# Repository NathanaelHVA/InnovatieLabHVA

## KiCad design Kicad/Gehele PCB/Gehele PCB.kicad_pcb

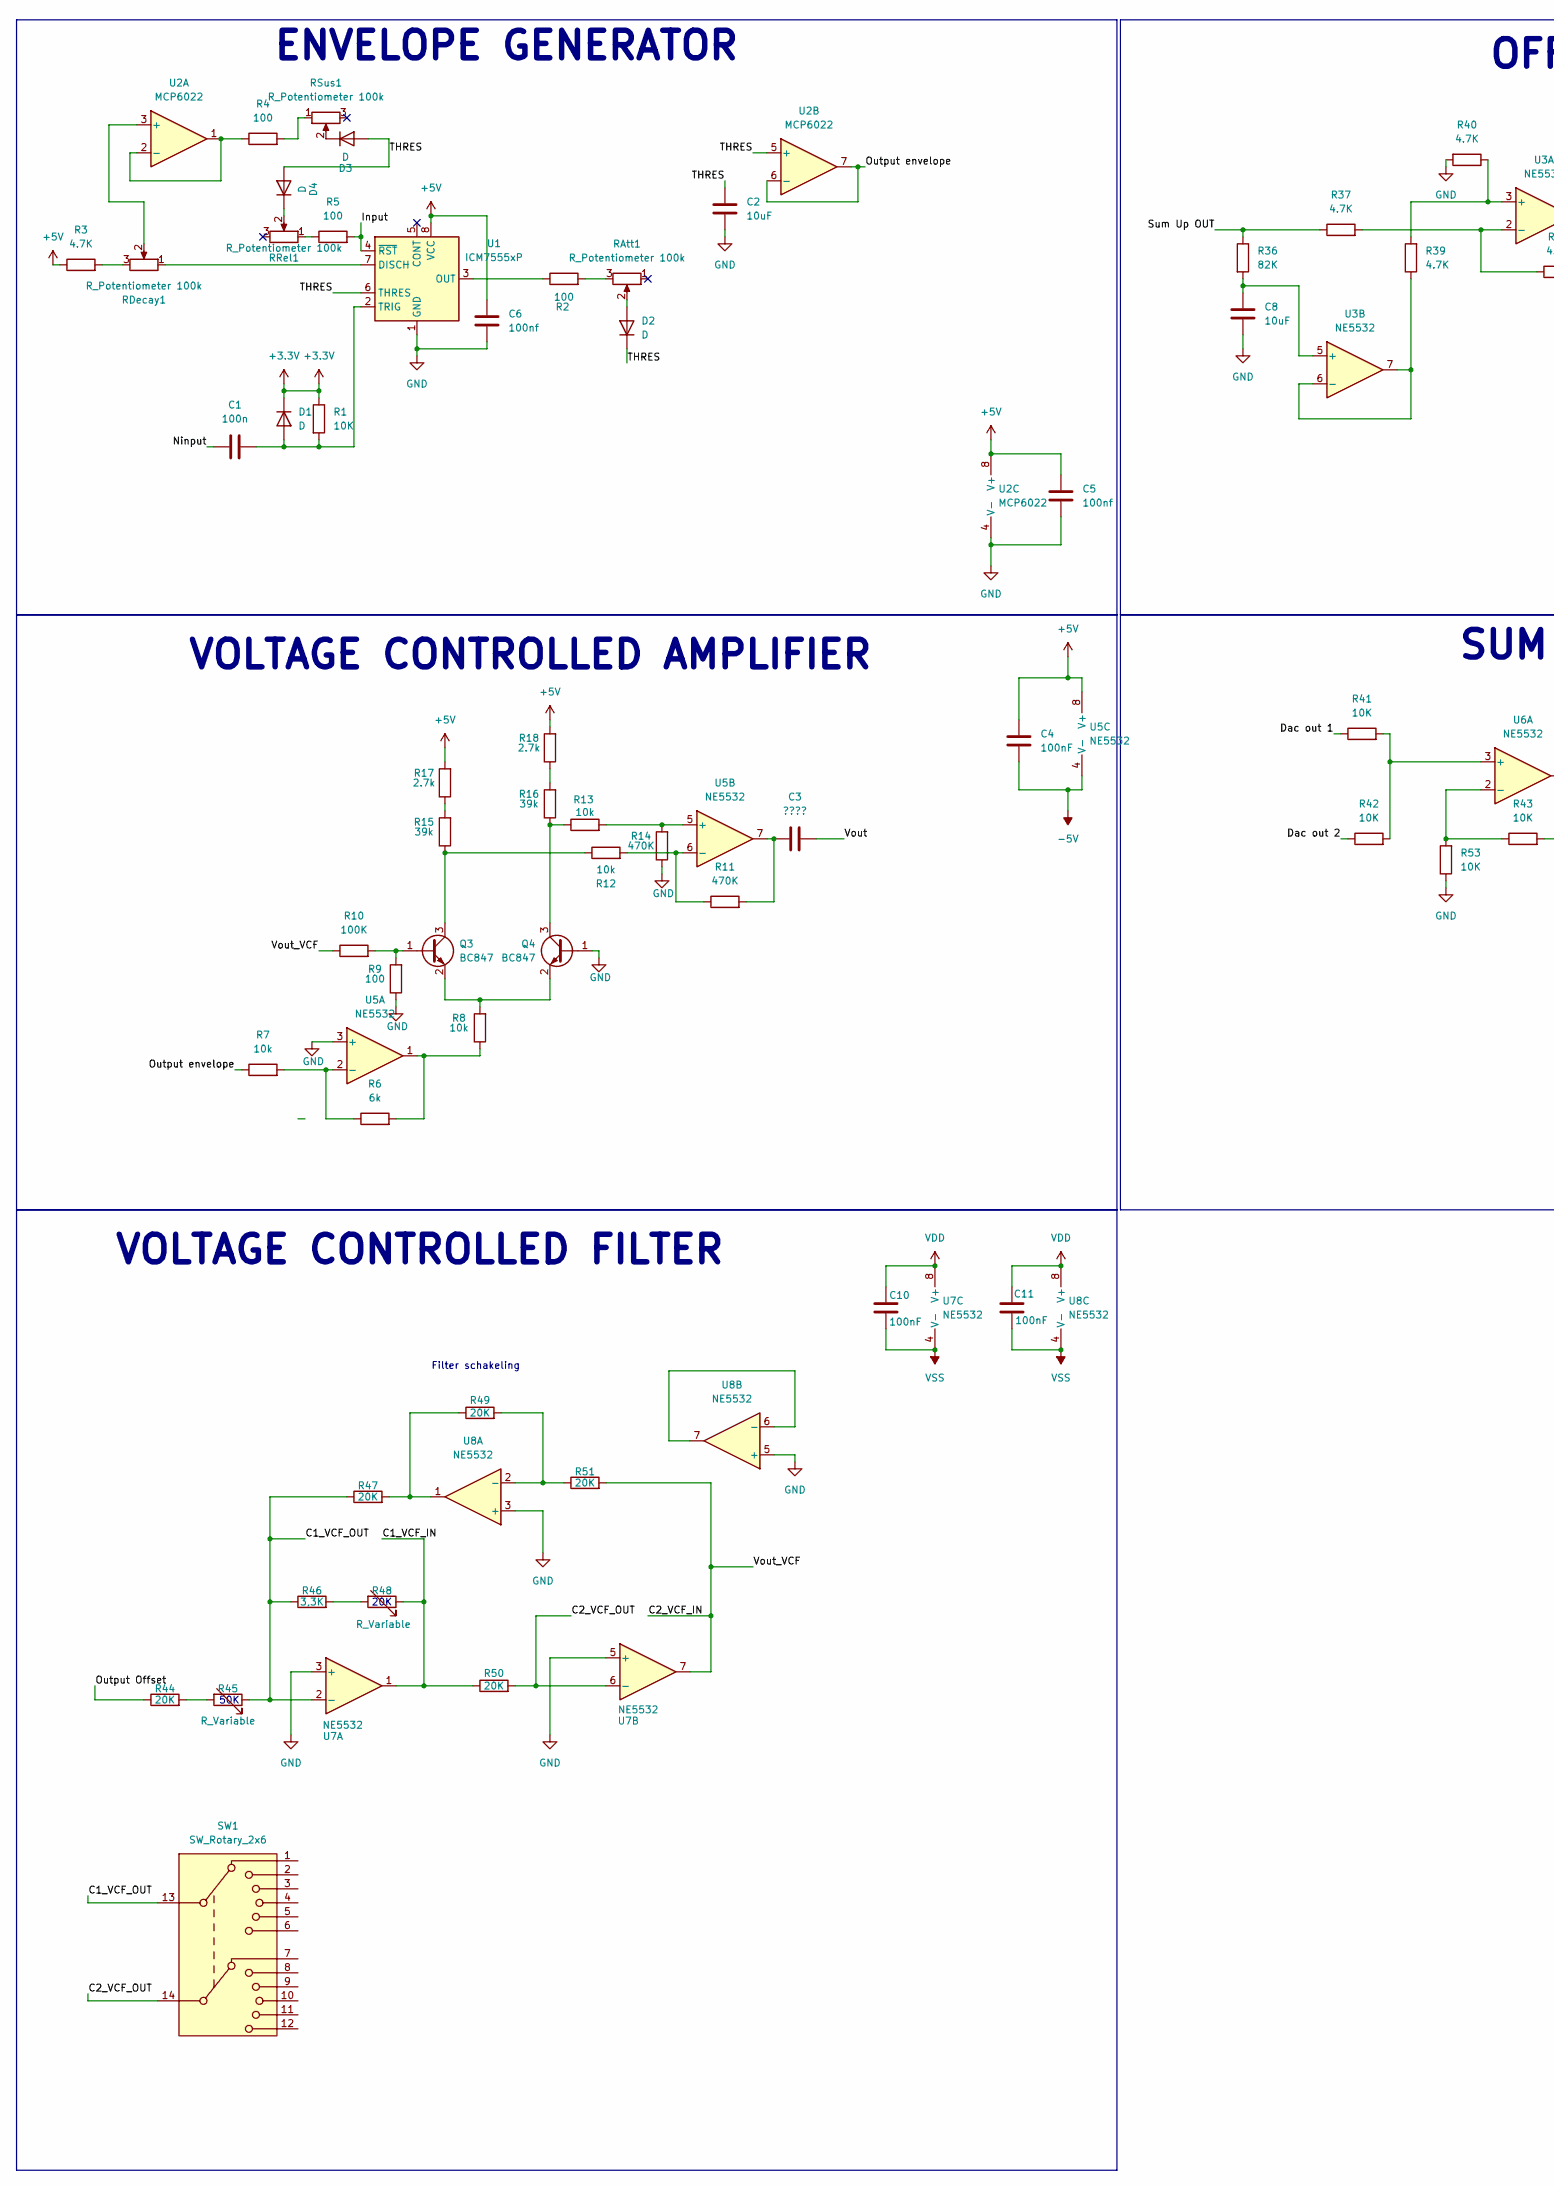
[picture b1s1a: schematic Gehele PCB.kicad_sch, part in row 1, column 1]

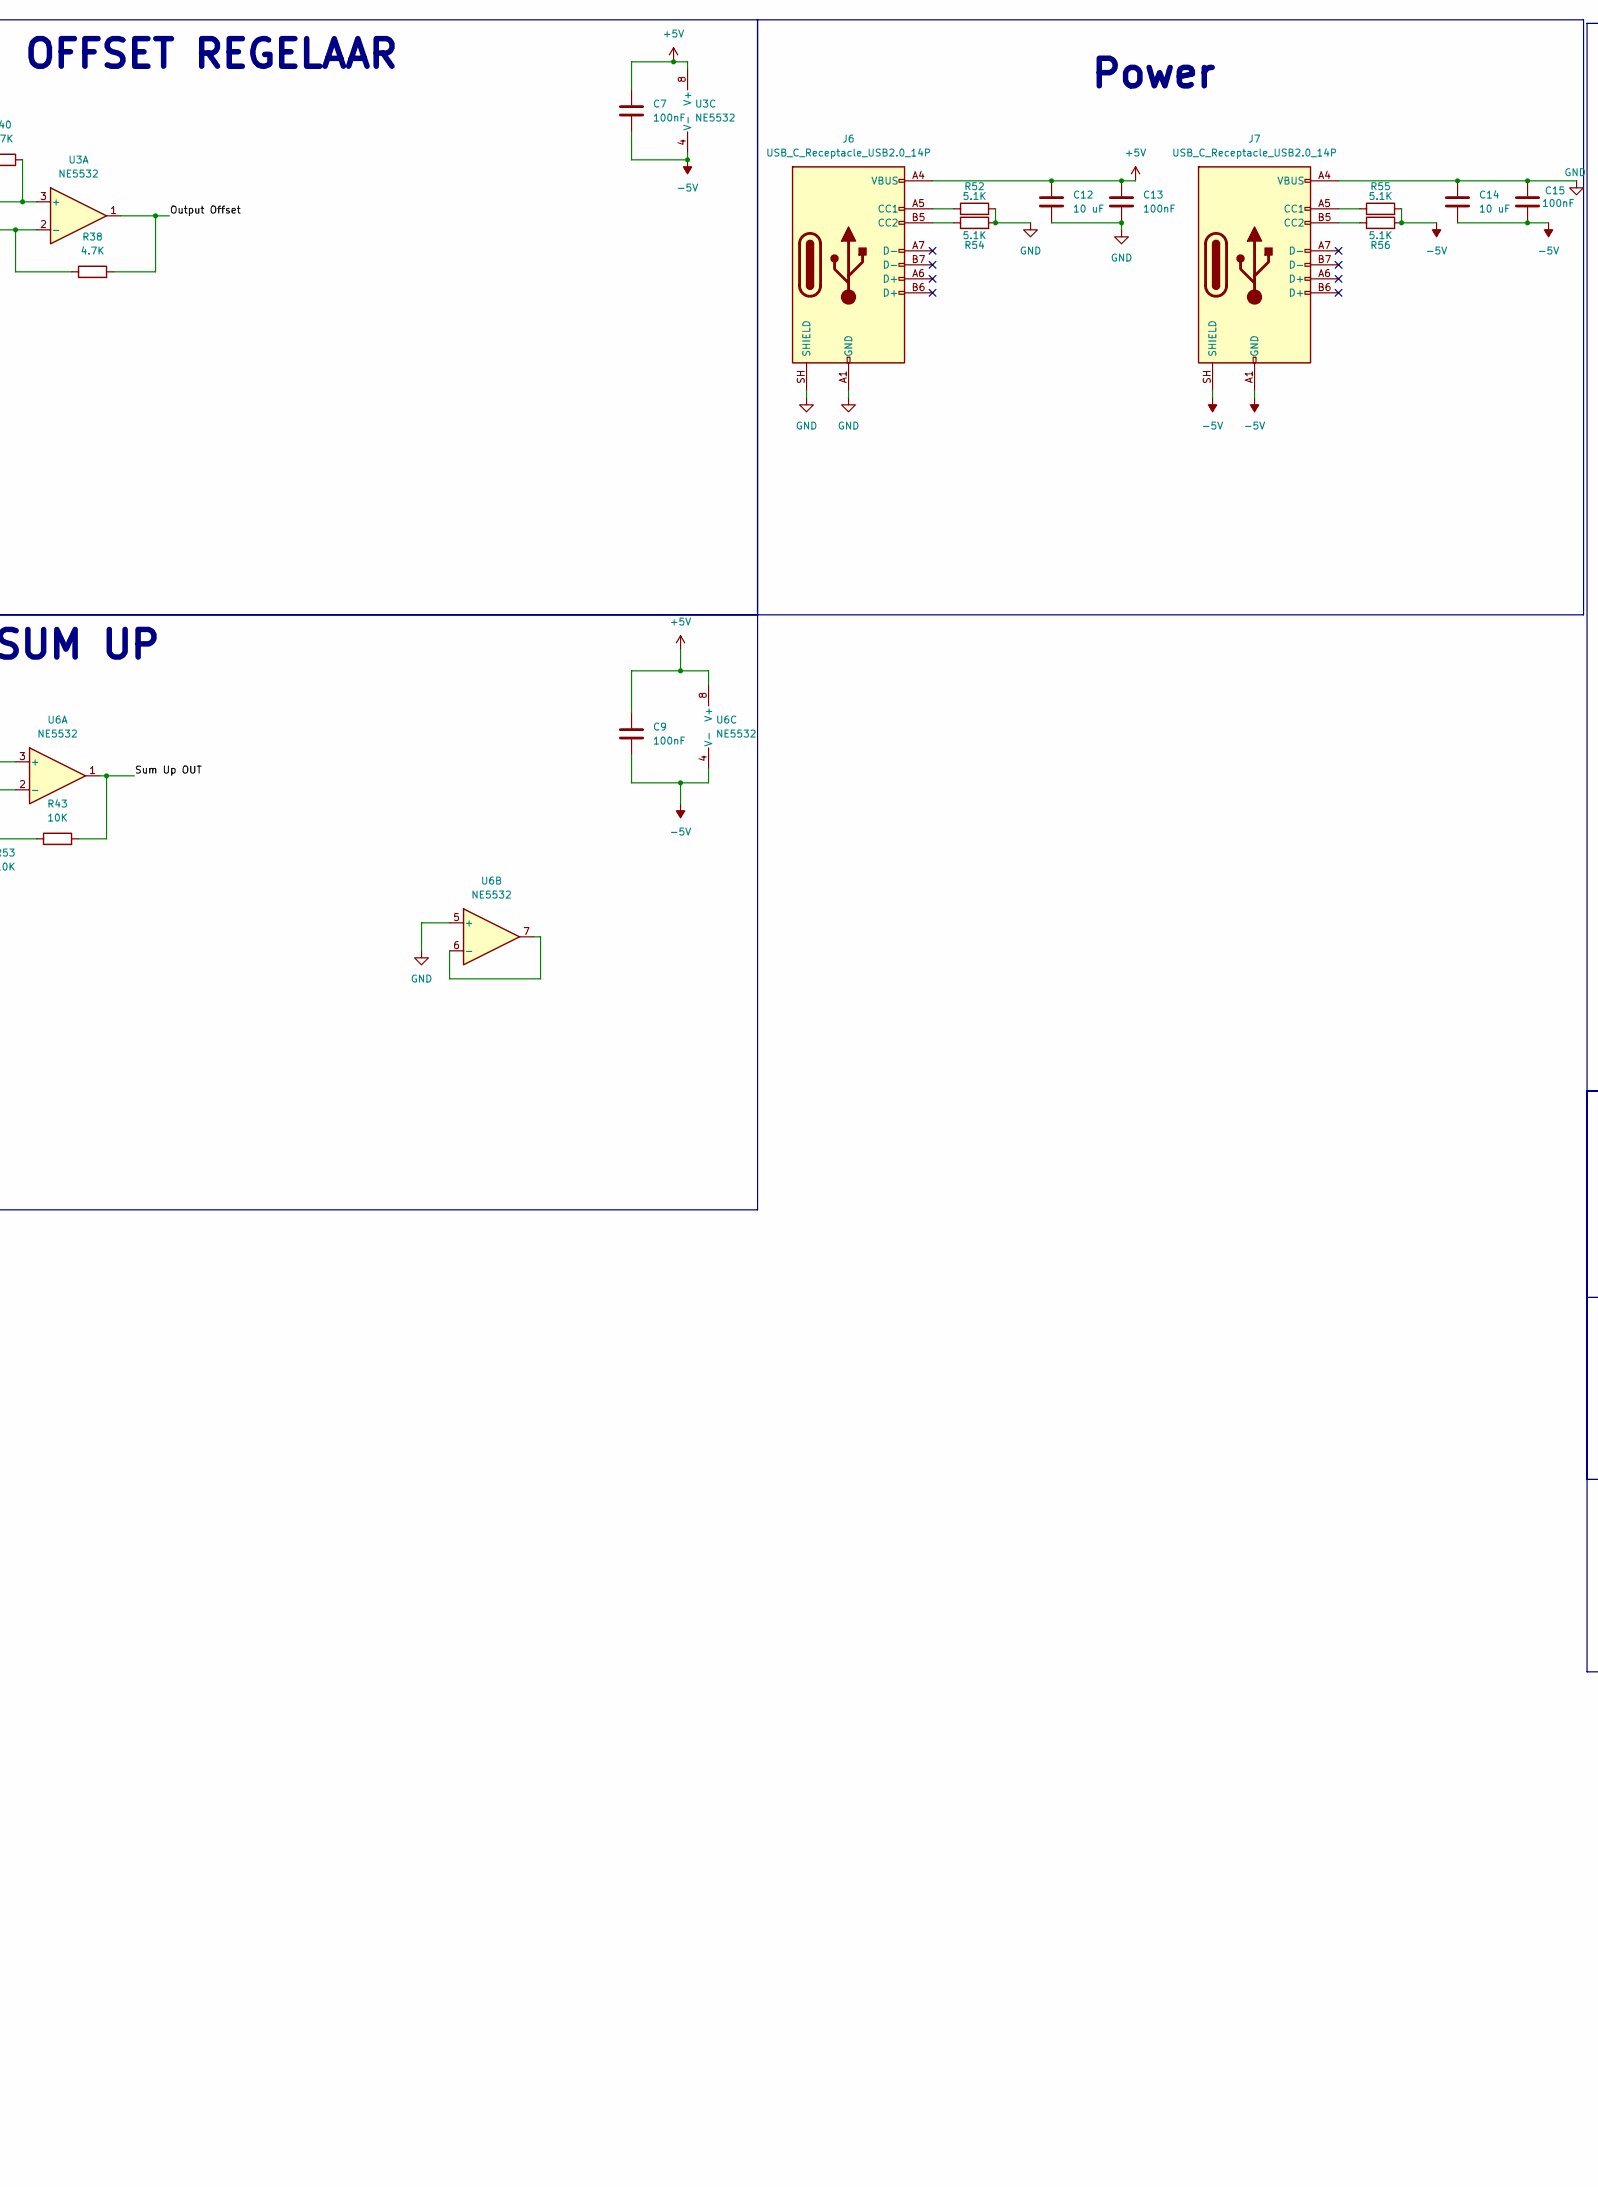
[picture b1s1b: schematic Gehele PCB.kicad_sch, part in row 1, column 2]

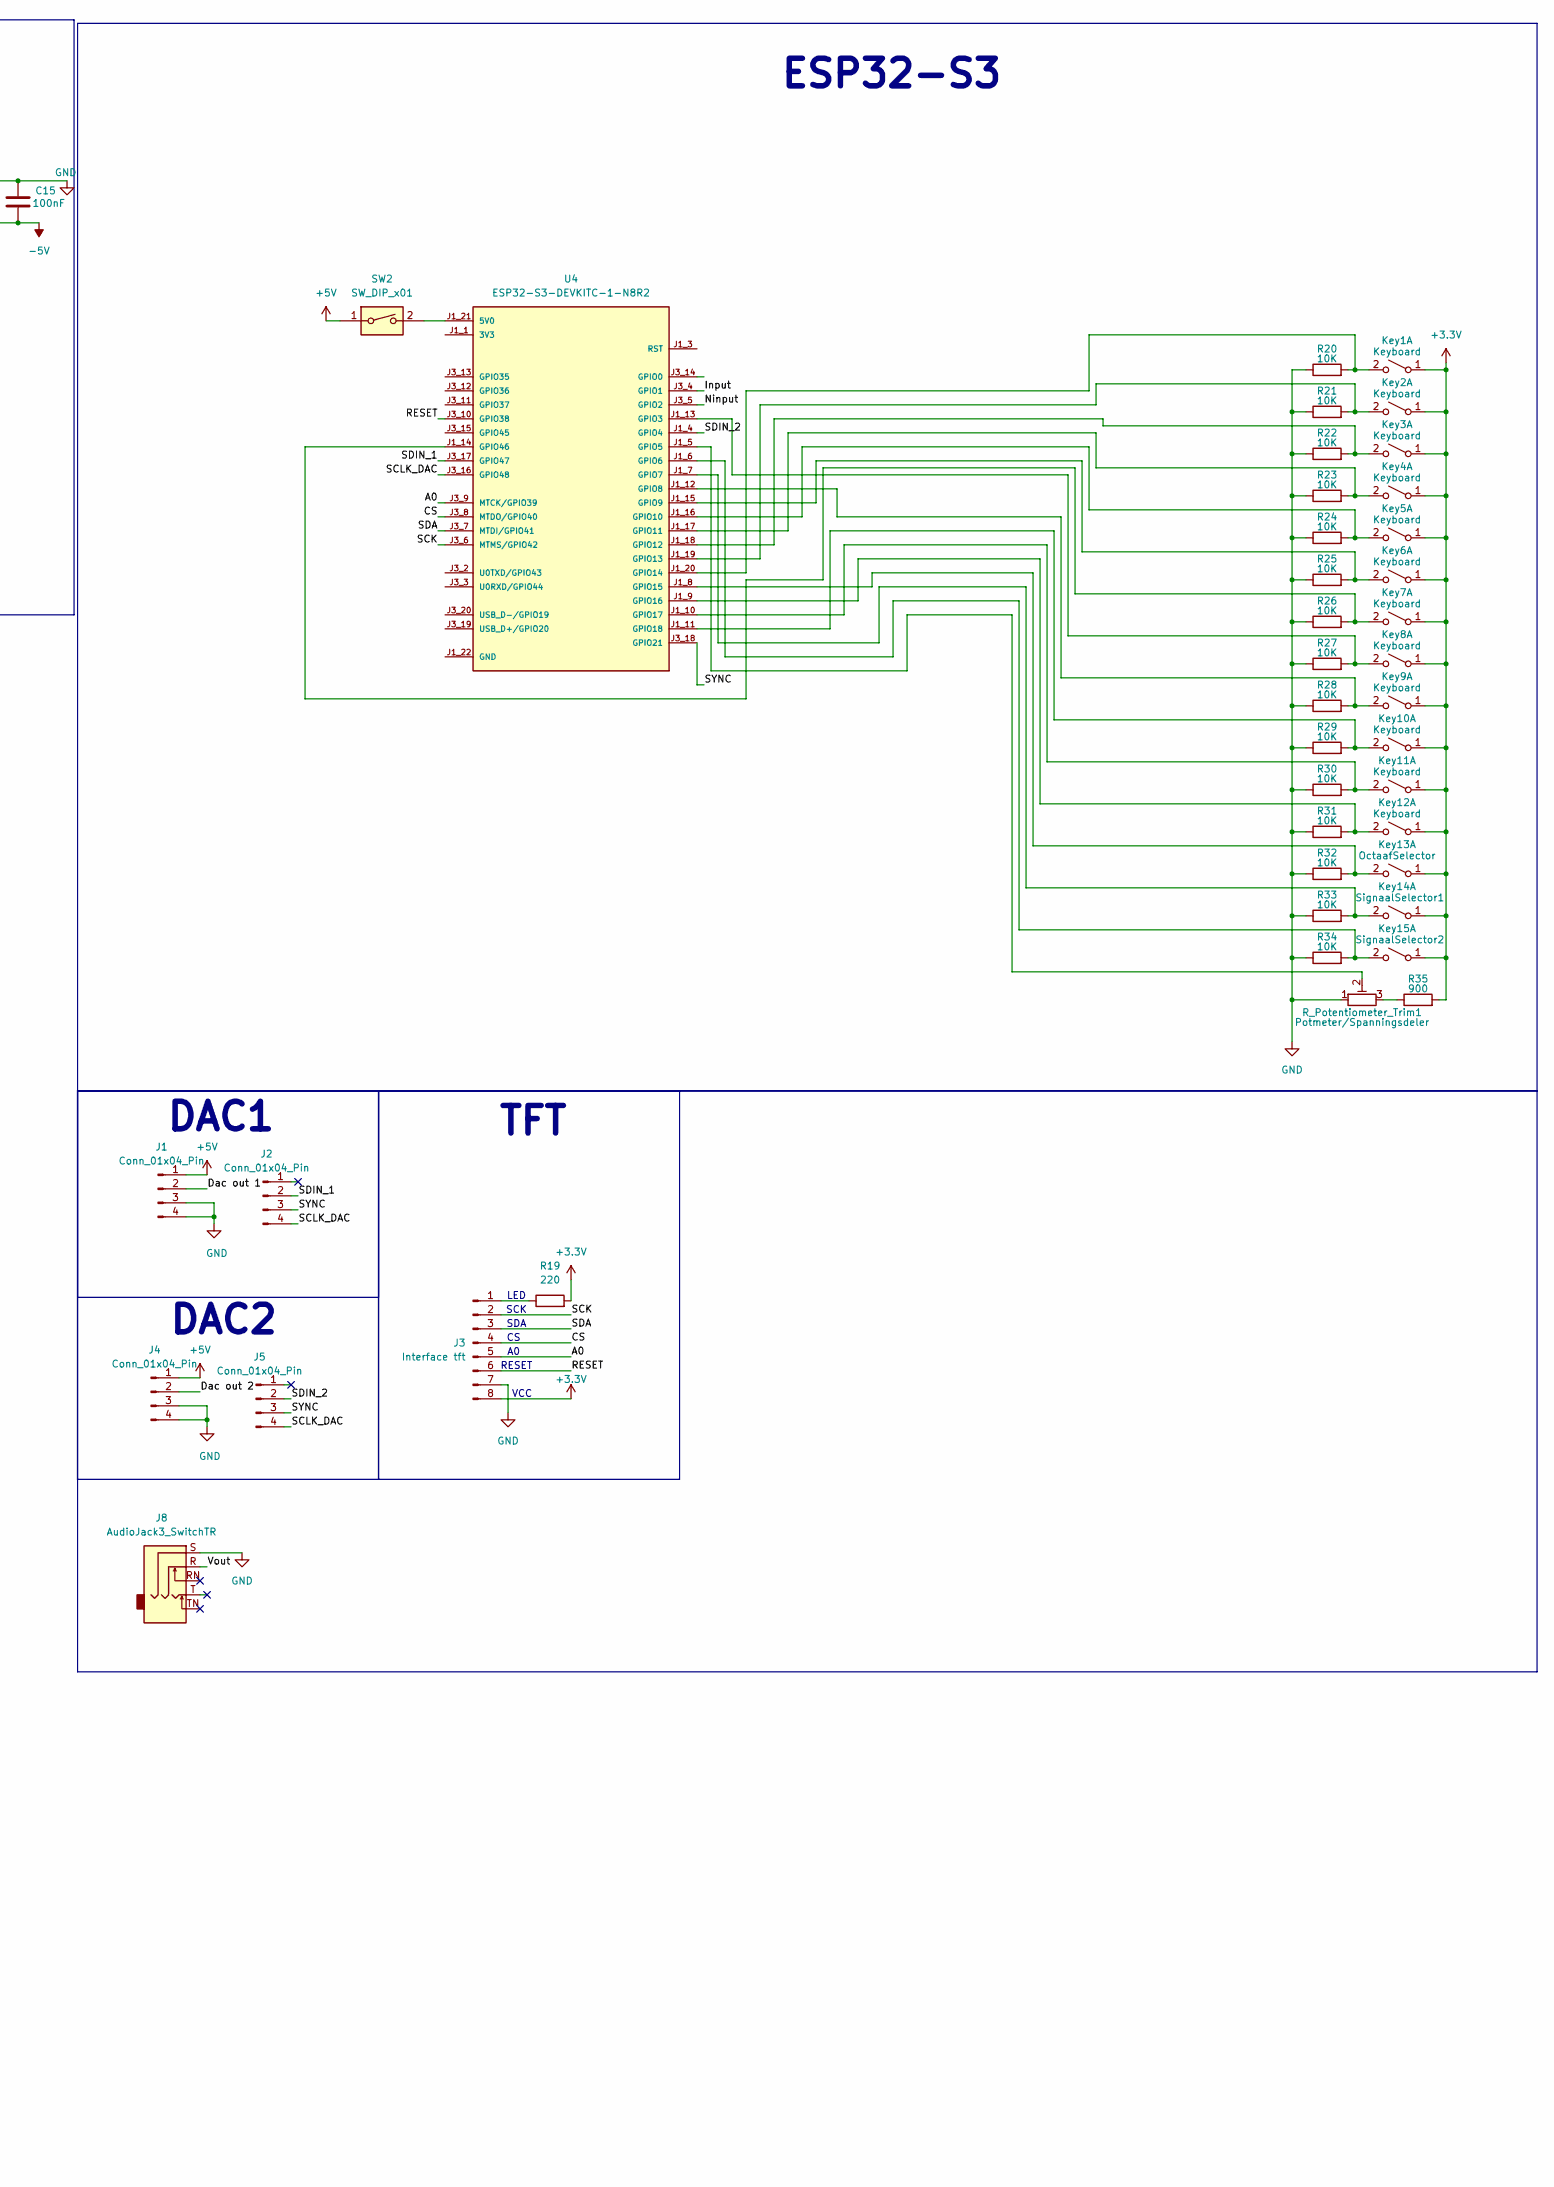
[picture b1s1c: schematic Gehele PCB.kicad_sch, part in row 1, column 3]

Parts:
C1: 100n; C_0805_2012Metric_Pad1.18x1.45mm_HandSolder
C2, C8: 10uF; C_0805_2012Metric_Pad1.18x1.45mm_HandSolder
C3: ????; C_0805_2012Metric_Pad1.18x1.45mm_HandSolder
C4, C7, C9, C10, C11, C13, C15: 100nF; C_0805_2012Metric_Pad1.18x1.45mm_HandSolder
C5, C6: 100nf; C_0805_2012Metric_Pad1.18x1.45mm_HandSolder
C12, C14: 10 uF; C_0805_2012Metric_Pad1.18x1.45mm_HandSolder
D1, D2, D3, D4: D; D_5W_P12.70mm_Horizontal
J1, J2, J4, J5: Conn_01x04_Pin; PinHeader_1x04_P2.54mm_Vertical
J3: Interface tft; PinHeader_1x08_P2.54mm_Vertical
J6, J7: USB_C_Receptacle_USB2.0_14P; USB_C_Receptacle_GCT_USB4125-xx-x_6P_TopMnt_Horizontal
J8: AudioJack3_SwitchTR; Jack_3.5mm_CUI_SJ1-3525N_Horizontal
Key1, Key2, Key3, Key4, Key5, Key6, Key7, Key8, Key9, Key10, Key11, Key12: Keyboard; SW_PUSH_6mm_H7.3mm
Key13: OctaafSelector; SW_PUSH_6mm_H7.3mm
Key14: SignaalSelector1; SW_PUSH_6mm_H7.3mm
Key15: SignaalSelector2; SW_PUSH_6mm_H7.3mm
Q3, Q4: BC847
R1, R20, R21, R22, R23, R24, R25, R26, R27, R28, R29, R30, R31, R32, R33, R34, R41, R42, R43, R53: 10K; R_0805_2012Metric_Pad1.20x1.40mm_HandSolder
R2, R4, R5: 100; R_0805_2012Metric_Pad1.20x1.40mm_HandSolder
R3, R37, R38, R39, R40: 4.7K; R_0805_2012Metric_Pad1.20x1.40mm_HandSolder
R6: 6k; C_0805_2012Metric_Pad1.18x1.45mm_HandSolder
R7, R8, R12, R13: 10k; C_0805_2012Metric_Pad1.18x1.45mm_HandSolder
R9: 100; C_0805_2012Metric_Pad1.18x1.45mm_HandSolder
R10: 100K; C_0805_2012Metric_Pad1.18x1.45mm_HandSolder
R11, R14: 470K; C_0805_2012Metric_Pad1.18x1.45mm_HandSolder
R15, R16: 39k; C_0805_2012Metric_Pad1.18x1.45mm_HandSolder
R17, R18: 2.7k; C_0805_2012Metric_Pad1.18x1.45mm_HandSolder
R19: 220; R_0805_2012Metric_Pad1.20x1.40mm_HandSolder
R35: 900; R_0805_2012Metric_Pad1.20x1.40mm_HandSolder
R36: 82K; R_0805_2012Metric_Pad1.20x1.40mm_HandSolder
R44, R47, R49, R50, R51: 20K; R_0805_2012Metric_Pad1.20x1.40mm_HandSolder
R45, R48: R_Variable; Potentiometer_Piher_PT-10-V10_Vertical
R46: 3,3K; R_0805_2012Metric_Pad1.20x1.40mm_HandSolder
R52, R54, R55, R56: 5.1K; R_0805_2012Metric_Pad1.20x1.40mm_HandSolder
RAtt1: R_Potentiometer 100k; Potentiometer_Piher_PT-10-V10_Vertical
RDecay1: R_Potentiometer 100k; Potentiometer_Piher_PT-10-V10_Vertical
RRel1: R_Potentiometer 100k; Potentiometer_Piher_PT-10-V10_Vertical
RSus1: R_Potentiometer 100k; Potentiometer_Piher_PT-10-V10_Vertical
R_Potentiometer_Trim1: Potmeter/Spanningsdeler; Potentiometer_Piher_PT-10-H05_Horizontal
SW1: SW_Rotary_2x6
SW2: SW_DIP_x01
U1: ICM7555xP; DIP-8_W7.62mm
U2: MCP6022; SOIC-8_3.9x4.9mm_P1.27mm
U3, U5, U6, U7, U8: NE5532; SOIC-8_3.9x4.9mm_P1.27mm
U4: ESP32-S3-DEVKITC-1-N8R2; ESP32-S3-Wroom-1 N16R8; PARTREV V1

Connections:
3V3: U4.J1_1 (3V3), U4.J1_2 (3V3)
+3.3V: D1.1 (K), J3.8, Key1.1 (A), Key2.1 (A), Key3.1 (A), Key4.1 (A), Key5.1 (A), Key6.1 (A), Key7.1 (A), Key8.1 (A), Key9.1 (A), Key10.1 (A), Key11.1 (A), Key12.1 (A), Key13.1 (A), Key14.1 (A), Key15.1 (A), R1.1, R19.2, R35.2
+5V: C4.2, C5.2, C6.2, C7.2, C9.2, C12.1, C13.1, J1.1, J4.1, J6.A4 (VBUS), J6.A9 (VBUS), J6.B4 (VBUS), J6.B9 (VBUS), R3.1, R17.2, R18.2, SW2.1, U1.8 (VCC), U2.8 (V+), U3.8 (V+), U5.8 (V+), U6.8 (V+)
-5V: C4.1, C7.1, C9.1, C14.2, C15.2, J7.A1 (GND), J7.A12 (GND), J7.B1 (GND), J7.B12 (GND), J7.SH (SHIELD), R55.2, R56.2, U3.4 (V-), U5.4 (V-), U6.4 (V-)
/A0: J3.5, U4.J3_9 (MTCK/GPIO39)
/C1_VCF_IN: R48.1, R50.1, U7.1
/C1_VCF_OUT: R45.1, R46.1, R47.1, SW1.13, U7.2 (-)
/C2_VCF_IN: R10.1, R51.2, U7.7
/C2_VCF_OUT: R50.2, SW1.14, U7.6 (-)
/CS: J3.4, U4.J3_8 (MTDO/GPIO40)
/Dac out 1: J1.2, R41.1
/Dac out 2: J4.2, R42.1
/Input: R5.2, U1.4 (~RST), U4.J3_4 (GPIO1)
/Ninput: C1.1, U4.J3_5 (GPIO2)
/Output Offset: R38.2, R44.1, U3.1
/Output envelope: R7.1, U2.6 (-), U2.7
/RESET: J3.6, U4.J3_10 (GPIO38)
/SCK: J3.2, U4.J3_6 (MTMS/GPIO42)
/SCLK_DAC: J2.4, J5.4, U4.J3_16 (GPIO48)
/SDA: J3.3, U4.J3_7 (MTDI/GPIO41)
/SDIN_1: J2.2, U4.J3_17 (GPIO47)
/SDIN_2: J5.2, U4.J1_4 (GPIO4)
/SYNC: J2.3, J5.3, U4.J3_18 (GPIO21)
/Sum Up OUT: R36.1, R37.1, R43.2, U6.1
/THRES: C2.2, D2.1 (K), D3.2 (A), D4.2 (A), U1.6 (THRES), U2.5 (+)
/Vout: C3.2, J8.R
unnamed: C3.1, R11.2, U5.7
unnamed: C1.2, D1.2 (A), R1.2, U1.2 (TRIG)
unnamed: D2.2 (A), RAtt1.2
unnamed: D3.1 (K), RSus1.2
unnamed: D4.1 (K), RRel1.2
unnamed: J3.1, R19.1
unnamed: J6.A5 (CC1), R52.1
unnamed: J6.B5 (CC2), R54.1
unnamed: J7.A5 (CC1), R55.1
unnamed: J7.B5 (CC2), R56.1
unnamed: Key1.2 (B), R20.2, U4.J1_20 (GPIO14)
unnamed: Key2.2 (B), R21.2, U4.J1_19 (GPIO13)
unnamed: Key3.2 (B), R22.2, U4.J1_18 (GPIO12)
unnamed: Key4.2 (B), R23.2, U4.J1_17 (GPIO11)
unnamed: Key5.2 (B), R24.2, U4.J1_16 (GPIO10)
unnamed: Key6.2 (B), R25.2, U4.J1_15 (GPIO9)
unnamed: Key7.2 (B), R26.2, U4.J1_14 (GPIO46)
unnamed: Key8.2 (B), R27.2, U4.J1_13 (GPIO3)
unnamed: Key9.2 (B), R28.2, U4.J1_12 (GPIO8)
unnamed: Key10.2 (B), R29.2, U4.J1_11 (GPIO18)
unnamed: Key11.2 (B), R30.2, U4.J1_10 (GPIO17)
unnamed: Key12.2 (B), R31.2, U4.J1_9 (GPIO16)
unnamed: Key13.2 (B), R32.2, U4.J1_8 (GPIO15)
unnamed: Key14.2 (B), R33.2, U4.J1_7 (GPIO7)
unnamed: Key15.2 (B), R34.2, U4.J1_6 (GPIO6)
unnamed: Q3.1 (B), R9.2, R10.2
unnamed: Q3.3 (C), R12.1, R15.1
unnamed: Q3.2 (E), Q4.2 (E), R8.2
unnamed: Q4.3 (C), R13.1, R16.1
unnamed: R2.2, RAtt1.3
unnamed: R3.2, RDecay1.3
unnamed: R4.2, RSus1.1
unnamed: R5.1, RRel1.1
unnamed: R6.2, R8.1, U5.1
unnamed: R15.2, R17.1
unnamed: R16.2, R18.1
unnamed: R35.1, R_Potentiometer_Trim1.3
unnamed: R44.2, R45.2
unnamed: R46.2, R48.2
unnamed: R47.2, R49.1, U8.1
unnamed: RDecay1.1, U1.7 (DISCH)
unnamed: R2.1, U1.3 (OUT)
unnamed: RDecay1.2, U2.3 (+)
unnamed: R4.1, U2.1, U2.2 (-)
unnamed: R39.2, R40.1, U3.3 (+)
unnamed: R37.2, R38.1, U3.2 (-)
unnamed: C8.1, R36.2, U3.5 (+)
unnamed: R39.1, U3.6 (-), U3.7
unnamed: SW2.2, U4.J1_21 (5V0)
unnamed: R_Potentiometer_Trim1.2, U4.J1_5 (GPIO5)
unnamed: R6.1, R7.2, U5.2 (-)
unnamed: R13.2, R14.2, U5.5 (+)
unnamed: R11.1, R12.2, U5.6 (-)
unnamed: R41.2, R42.2, U6.3 (+)
unnamed: R43.1, R53.2, U6.2 (-)
unnamed: U6.6 (-), U6.7
unnamed: R49.2, R51.1, U8.2 (-)
unnamed: U8.6 (-), U8.7
VDD: C10.1, C11.1, U7.8 (V+), U8.8 (V+)
VSS: C10.2, C11.2, U7.4 (V-), U8.4 (V-)

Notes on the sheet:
20K
Power
RESET
OFFSET REGELAAR
VOLTAGE CONTROLLED FILTER
VCC
SCK
ESP32-S3
DAC2
50K
SUM UP
ENVELOPE GENERATOR
DAC1
TFT
Filter schakeling
LED
VOLTAGE CONTROLLED AMPLIFIER
SDA

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
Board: 2 copper layers, 113 parts (1 on the bottom side), 86 nets, no tracks yet.

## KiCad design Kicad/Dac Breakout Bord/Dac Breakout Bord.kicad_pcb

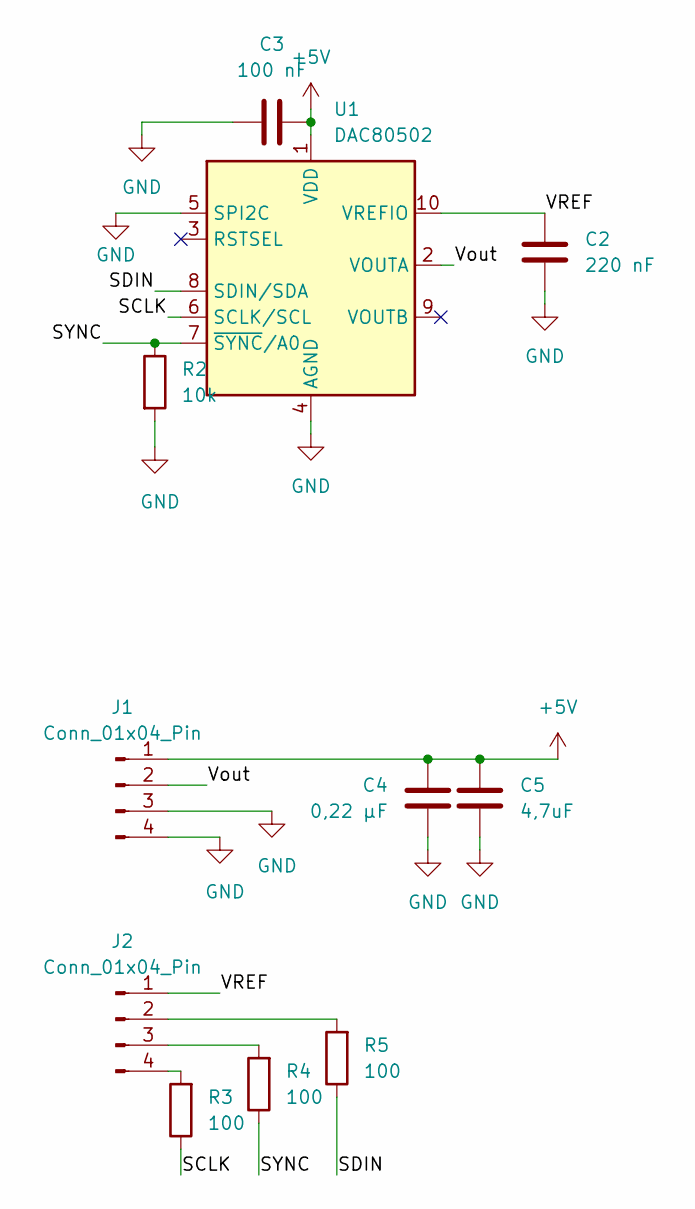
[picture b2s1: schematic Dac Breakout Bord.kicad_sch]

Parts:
C2: 220 nF; C_0805_2012Metric_Pad1.18x1.45mm_HandSolder
C3: 100 nF; C_0805_2012Metric_Pad1.18x1.45mm_HandSolder
C4: 0,22 µF; C_0805_2012Metric_Pad1.18x1.45mm_HandSolder
C5: 4,7uF; C_0805_2012Metric_Pad1.18x1.45mm_HandSolder
J1, J2: Conn_01x04_Pin; PinHeader_1x04_P2.54mm_Vertical
R2: 10k; R_0805_2012Metric_Pad1.20x1.40mm_HandSolder
R3, R4, R5: 100; R_0805_2012Metric_Pad1.20x1.40mm_HandSolder
U1: DAC80502; TSSOP-10_3x3mm_P0.5mm

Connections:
+5V: C3.2, C4.2, C5.2, J1.1, U1.1 (VDD)
/SCLK: R3.1, U1.6 (SCLK/SCL)
/SDIN: R5.1, U1.8 (SDIN/SDA)
/SYNC: R2.1, R4.1, U1.7 (~SYNC/A0)
/VREF: C2.1, J2.1, U1.10 (VREFIO)
/Vout: J1.2, U1.2 (VOUTA)
GND: C2.2, C3.1, C4.1, C5.1, J1.3, J1.4, R2.2, U1.4 (AGND), U1.5 (SPI2C)
unnamed: J2.2, R5.2
unnamed: J2.3, R4.2
unnamed: J2.4, R3.2

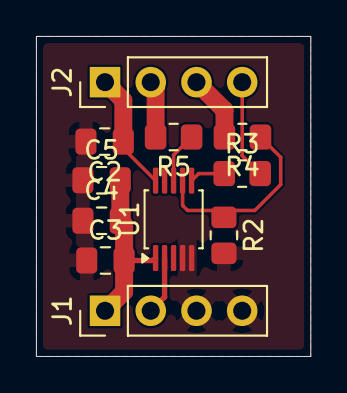
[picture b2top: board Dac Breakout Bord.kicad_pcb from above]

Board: 2 copper layers, 15.2 x 17.8 mm, 11 parts (0 on the bottom side), 10 nets.

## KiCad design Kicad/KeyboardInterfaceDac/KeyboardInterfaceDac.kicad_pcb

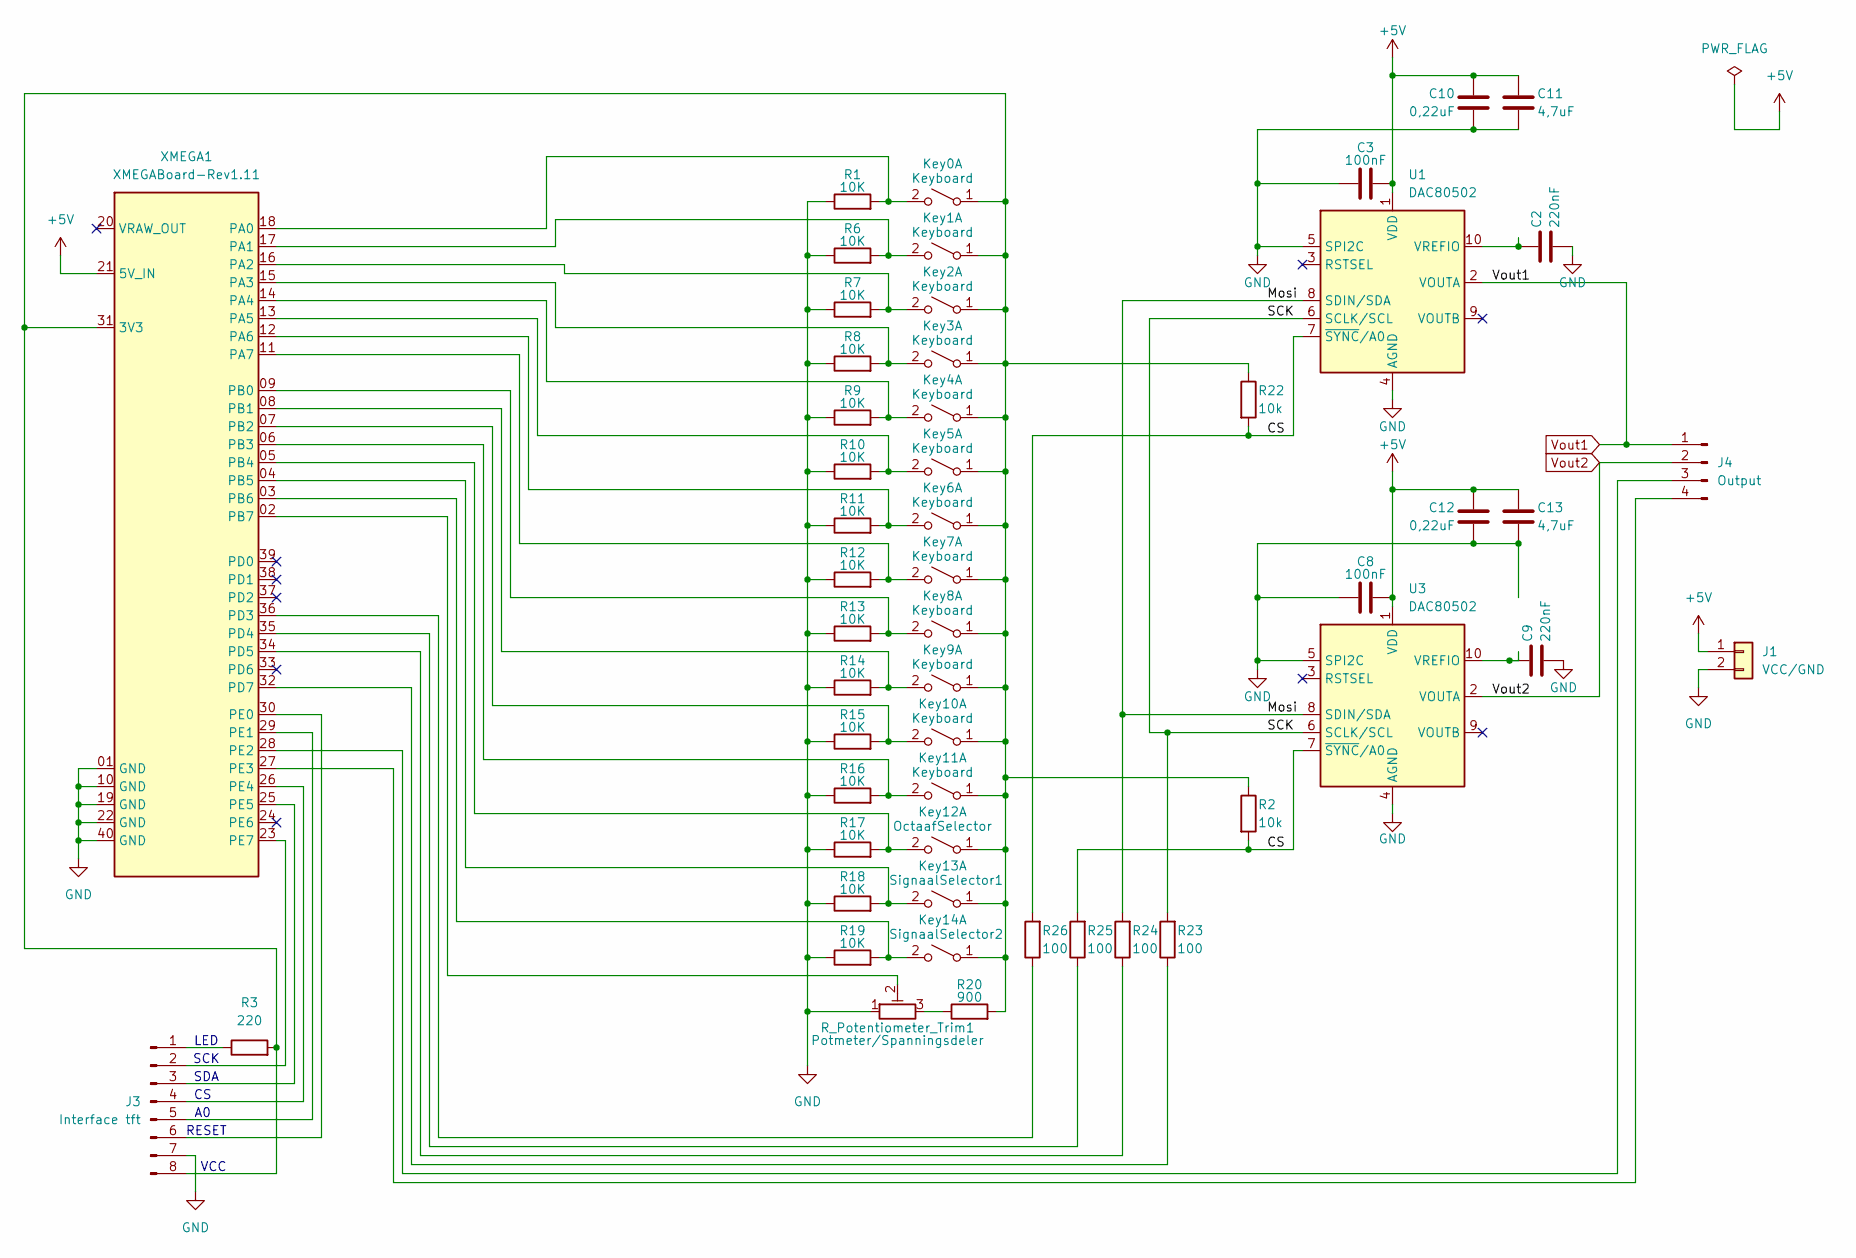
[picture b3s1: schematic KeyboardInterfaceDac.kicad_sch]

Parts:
C2, C9: 220nF; C_0805_2012Metric_Pad1.18x1.45mm_HandSolder
C3, C8: 100nF; C_0805_2012Metric_Pad1.18x1.45mm_HandSolder
C10, C12: 0,22uF; C_0805_2012Metric_Pad1.18x1.45mm_HandSolder
C11, C13: 4,7uF; C_0805_2012Metric_Pad1.18x1.45mm_HandSolder
J1: VCC/GND; CON_2057-EBBA-02-C-SS-BU
J3: Interface tft; PinHeader_1x08_P2.54mm_Vertical
J4: Output; PinSocket_1x04_P2.54mm_Vertical
Key0, Key1, Key2, Key3, Key4, Key5, Key6, Key7, Key8, Key9, Key10, Key11: Keyboard; SW_PUSH_6mm_H7.3mm
Key12: OctaafSelector; SW_PUSH_6mm_H7.3mm
Key13: SignaalSelector1; SW_PUSH_6mm_H7.3mm
Key14: SignaalSelector2; SW_PUSH_6mm_H7.3mm
R1, R6, R7, R8, R9, R10, R11, R12, R13, R14, R15, R16, R17, R18, R19: 10K; R_0805_2012Metric_Pad1.20x1.40mm_HandSolder
R2, R22: 10k; R_Axial_DIN0207_L6.3mm_D2.5mm_P7.62mm_Horizontal
R3: 220; R_0805_2012Metric_Pad1.20x1.40mm_HandSolder
R20: 900; R_0805_2012Metric_Pad1.20x1.40mm_HandSolder
R23, R24: 100; R_Axial_DIN0207_L6.3mm_D2.5mm_P7.62mm_Horizontal
R25, R26: 100; R_0805_2012Metric_Pad1.20x1.40mm_HandSolder
R_Potentiometer_Trim1: Potmeter/Spanningsdeler; Potentiometer_Piher_PT-10-H05_Horizontal
U1, U3: DAC80502; TSSOP-10_3x3mm_P0.5mm
XMEGA1: XMEGABoard-Rev1.11; HvA_XMEGABoard-rev1.00-S

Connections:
+5V: C3.2, C8.2, C10.2, C11.2, C12.2, C13.2, J1.1, U1.1 (VDD), U3.1 (VDD), XMEGA1.21 (5V_IN)
/CS: R2.2, R22.2, R25.2, R26.2, U1.7 (~SYNC/A0), U3.7 (~SYNC/A0)
/Mosi: R24.2, U1.8 (SDIN/SDA), U3.8 (SDIN/SDA)
/SCK: R23.2, U1.6 (SCLK/SCL), U3.6 (SCLK/SCL)
GND: C2.2, C3.1, C8.1, C9.2, C10.1, C11.1, C12.1, C13.1, J1.2, J3.7, R1.1, R6.1, R7.1, R8.1, R9.1, R10.1, R11.1, R12.1, R13.1, R14.1, R15.1, R16.1, R17.1, R18.1, R19.1, R_Potentiometer_Trim1.1, U1.4 (AGND), U1.5 (SPI2C), U3.4 (AGND), U3.5 (SPI2C), XMEGA1.01 (GND), XMEGA1.10 (GND), XMEGA1.19 (GND), XMEGA1.22 (GND), XMEGA1.40 (GND)
unnamed: J3.1, R3.1
unnamed: J3.2, XMEGA1.23 (PE7)
unnamed: J3.3, XMEGA1.25 (PE5)
unnamed: J3.4, XMEGA1.26 (PE4)
unnamed: J3.5, XMEGA1.29 (PE1)
unnamed: J3.6, XMEGA1.30 (PE0)
unnamed: J3.8, Key0.1 (A), Key1.1 (A), Key2.1 (A), Key3.1 (A), Key4.1 (A), Key5.1 (A), Key6.1 (A), Key7.1 (A), Key8.1 (A), Key9.1 (A), Key10.1 (A), Key11.1 (A), Key12.1 (A), Key13.1 (A), Key14.1 (A), R2.1, R3.2, R20.2, R22.1, XMEGA1.31 (3V3)
unnamed: J4.3, XMEGA1.28 (PE2)
unnamed: J4.4, XMEGA1.27 (PE3)
unnamed: Key0.2 (B), R1.2, XMEGA1.18 (PA0)
unnamed: Key1.2 (B), R6.2, XMEGA1.17 (PA1)
unnamed: Key2.2 (B), R7.2, XMEGA1.16 (PA2)
unnamed: Key3.2 (B), R8.2, XMEGA1.15 (PA3)
unnamed: Key4.2 (B), R9.2, XMEGA1.14 (PA4)
unnamed: Key5.2 (B), R10.2, XMEGA1.13 (PA5)
unnamed: Key6.2 (B), R11.2, XMEGA1.12 (PA6)
unnamed: Key7.2 (B), R12.2, XMEGA1.11 (PA7)
unnamed: Key8.2 (B), R13.2, XMEGA1.09 (PB0)
unnamed: Key9.2 (B), R14.2, XMEGA1.08 (PB1)
unnamed: Key10.2 (B), R15.2, XMEGA1.07 (PB2)
unnamed: Key11.2 (B), R16.2, XMEGA1.06 (PB3)
unnamed: Key12.2 (B), R17.2, XMEGA1.05 (PB4)
unnamed: Key13.2 (B), R18.2, XMEGA1.04 (PB5)
unnamed: Key14.2 (B), R19.2, XMEGA1.03 (PB6)
unnamed: R20.1, R_Potentiometer_Trim1.3
unnamed: C2.1, U1.10 (VREFIO)
unnamed: C9.1, U3.10 (VREFIO)
unnamed: R_Potentiometer_Trim1.2, XMEGA1.02 (PB7)
unnamed: R26.1, XMEGA1.36 (PD3)
unnamed: R25.1, XMEGA1.35 (PD4)
unnamed: R24.1, XMEGA1.34 (PD5)
unnamed: R23.1, XMEGA1.32 (PD7)
Vout1: J4.1, U1.2 (VOUTA)
Vout2: J4.2, U3.2 (VOUTA)

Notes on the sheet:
VCC
RESET
SCK
SDA
LED

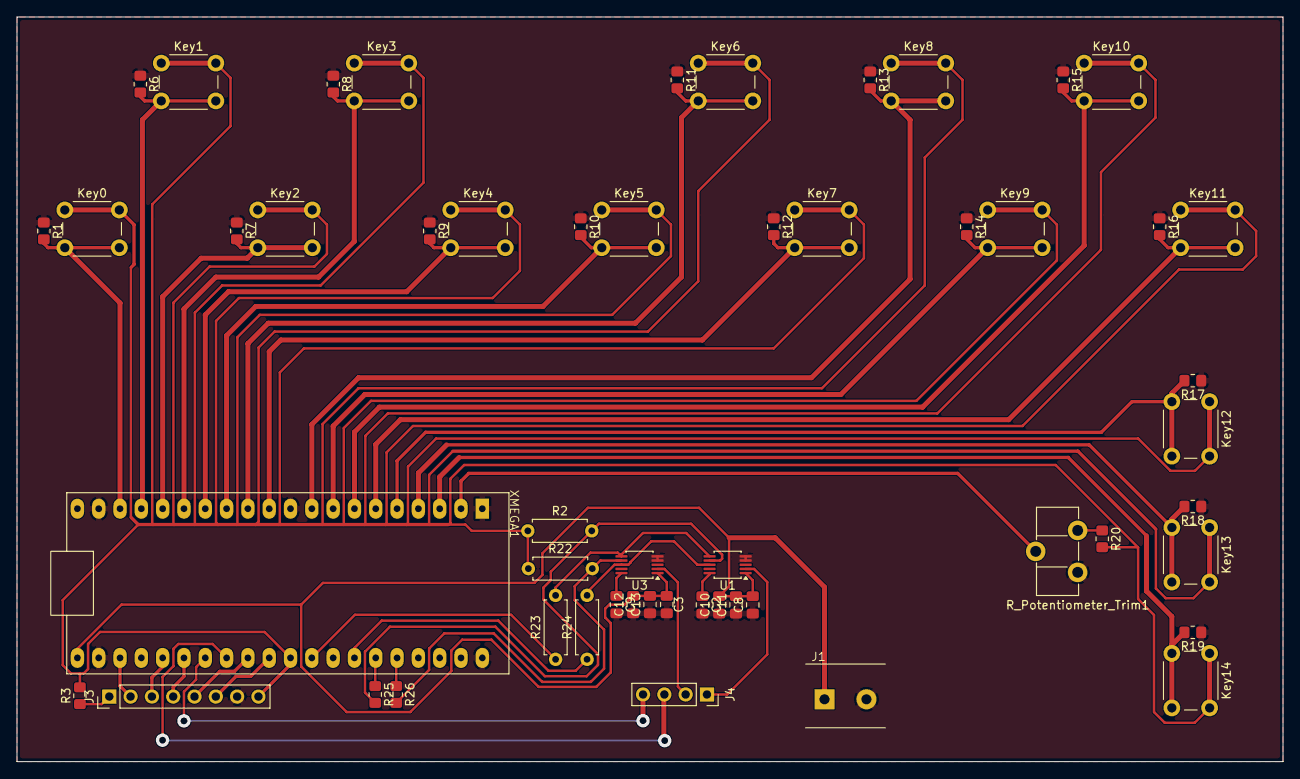
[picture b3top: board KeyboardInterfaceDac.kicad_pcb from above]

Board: 2 copper layers, 150.9 x 88.8 mm, 53 parts (0 on the bottom side), 39 nets.
